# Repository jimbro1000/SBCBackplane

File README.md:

# HD6309 SBC Backplane

This projects defines a backplane expansion system
for the HD6309 Single Board Computer I designed 
(see https://github.com/jimbro1000/HD6309sbc)

Each backplane panel provides two slots for the 
100mm x 100mm expansion tiles plus a pair of 
"sideways" connector to add extra backplane panels 
to either side.

Hypothetically you could keep expanding but in 
real terms the drivers on each chip can only 
connect to a limit number of other chips, this
places real term limits of 4 - 6 tiles without
buffering, especially on the address and data
lines

## Tile layout

The positioning of connectors for the tiles is
defined by the layout of the main SBC tile, as
such it is essential that the relative position
of the two power and expansion connector of each
tile is maintained

### Alternative layouts

Provided the relative tile connector positions are 
maintained the layout of boards does not need to
be two dimensional.

## Power input

All of the tiles (so far) require +5V and ground.
It is expected that the primary tile provides the
power input from an external source, with good
regulation of power and current. Adding extra
tiles may place unexpected load and cause drop
outs or unpredictable behaviours

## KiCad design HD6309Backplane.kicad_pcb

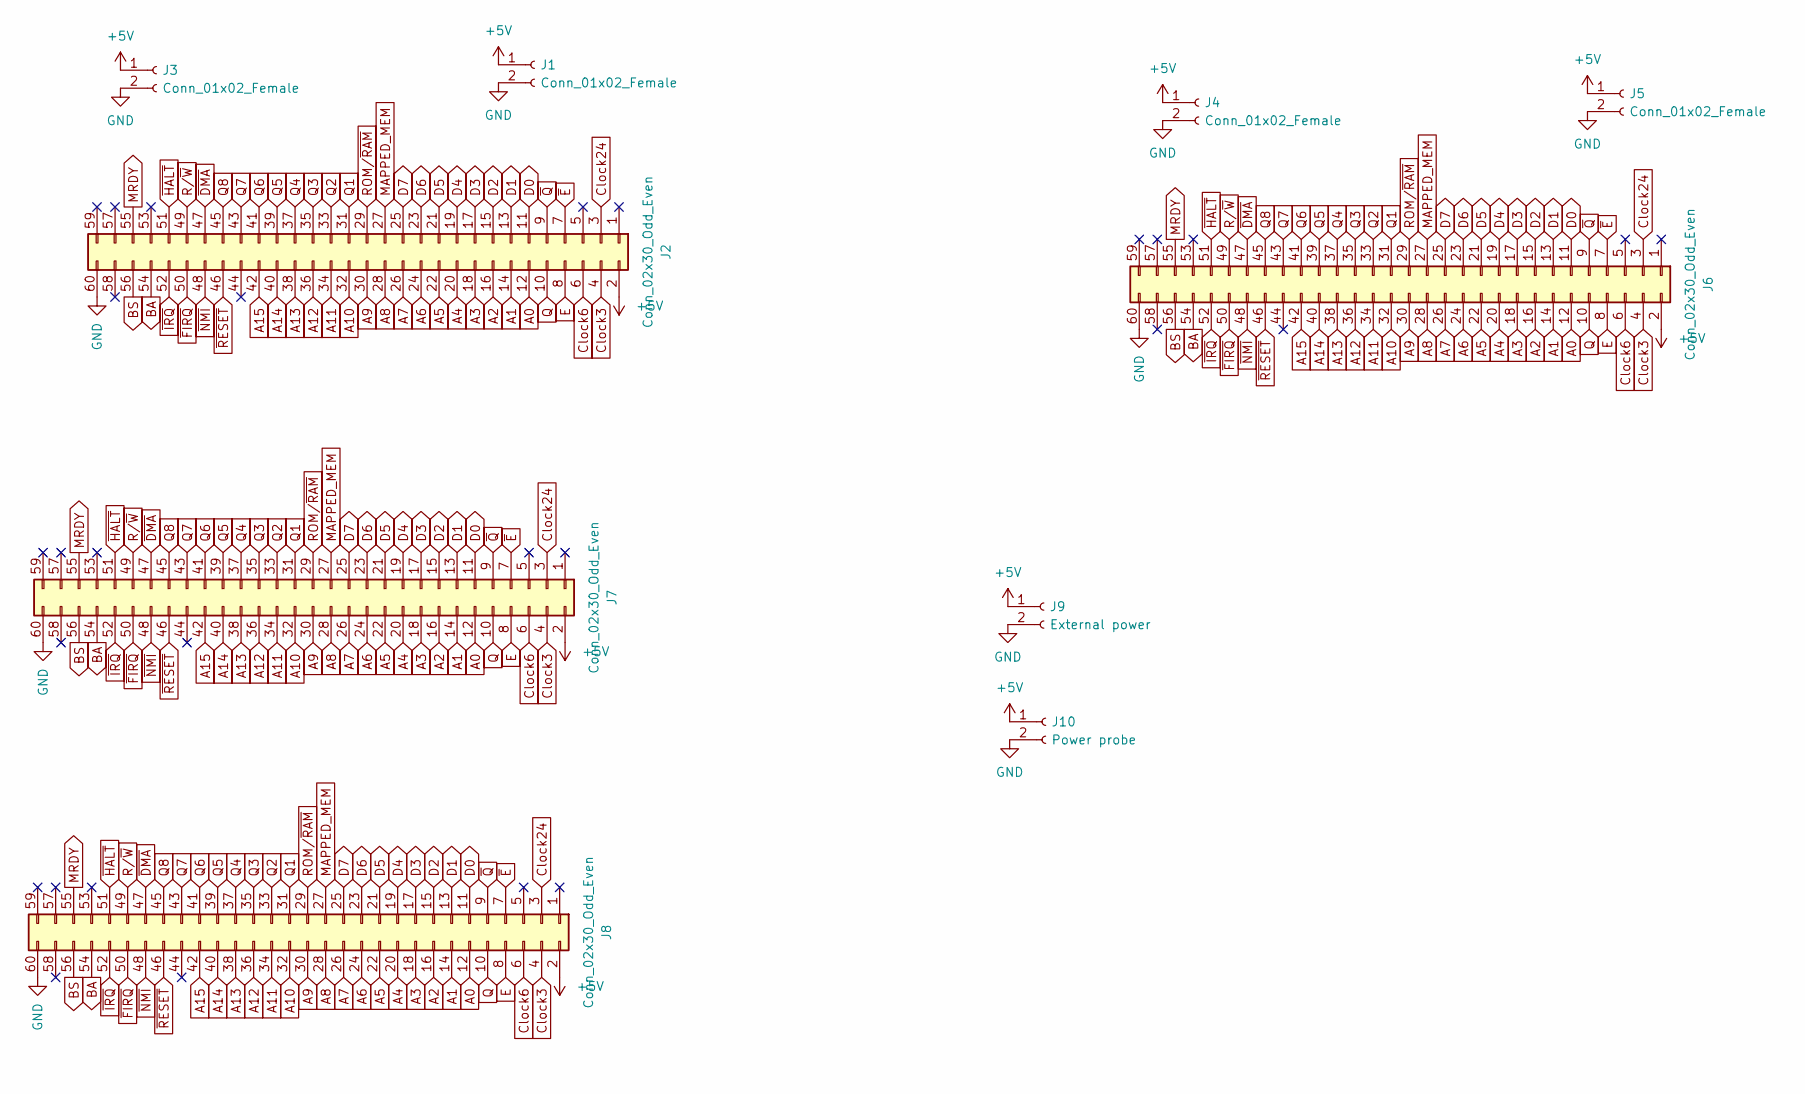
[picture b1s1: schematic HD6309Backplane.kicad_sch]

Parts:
J1, J3, J4, J5: Conn_01x02_Female; PinSocket_1x02_P2.54mm_Vertical
J2, J6, J7, J8: Conn_02x30_Odd_Even; PinSocket_2x30_P2.54mm_Vertical
J9: External power; PinSocket_1x02_P2.54mm_Vertical
J10: Power probe; PinSocket_1x02_P2.54mm_Vertical

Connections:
+5V: J1.1, J2.2, J3.1, J4.1, J5.1, J6.2, J7.2, J8.2, J9.1, J10.1
A0: J2.12, J6.12, J7.12, J8.12
A1: J2.14, J6.14, J7.14, J8.14
A2: J2.16, J6.16, J7.16, J8.16
A3: J2.18, J6.18, J7.18, J8.18
A4: J2.20, J6.20, J7.20, J8.20
A5: J2.22, J6.22, J7.22, J8.22
A6: J2.24, J6.24, J7.24, J8.24
A7: J2.26, J6.26, J7.26, J8.26
A8: J2.28, J6.28, J7.28, J8.28
A9: J2.30, J6.30, J7.30, J8.30
A10: J2.32, J6.32, J7.32, J8.32
A11: J2.34, J6.34, J7.34, J8.34
A12: J2.36, J6.36, J7.36, J8.36
A13: J2.38, J6.38, J7.38, J8.38
A14: J2.40, J6.40, J7.40, J8.40
A15: J2.42, J6.42, J7.42, J8.42
BA: J2.54, J6.54, J7.54, J8.54
BS: J2.56, J6.56, J7.56, J8.56
Clock3: J2.4, J6.4, J7.4, J8.4
Clock6: J2.6, J6.6, J7.6, J8.6
Clock24: J2.3, J6.3, J7.3, J8.3
D0: J2.11, J6.11, J7.11, J8.11
D1: J2.13, J6.13, J7.13, J8.13
D2: J2.15, J6.15, J7.15, J8.15
D3: J2.17, J6.17, J7.17, J8.17
D4: J2.19, J6.19, J7.19, J8.19
D5: J2.21, J6.21, J7.21, J8.21
D6: J2.23, J6.23, J7.23, J8.23
D7: J2.25, J6.25, J7.25, J8.25
E: J2.8, J6.8, J7.8, J8.8
GND: J1.2, J2.60, J3.2, J4.2, J5.2, J6.60, J7.60, J8.60, J9.2, J10.2
MAPPED_MEM: J2.27, J6.27, J7.27, J8.27
MRDY: J2.55, J6.55, J7.55, J8.55
Q: J2.10, J6.10, J7.10, J8.10
Q1: J2.31, J6.31, J7.31, J8.31
Q2: J2.33, J6.33, J7.33, J8.33
Q3: J2.35, J6.35, J7.35, J8.35
Q4: J2.37, J6.37, J7.37, J8.37
Q5: J2.39, J6.39, J7.39, J8.39
Q6: J2.41, J6.41, J7.41, J8.41
Q7: J2.43, J6.43, J7.43, J8.43
Q8: J2.45, J6.45, J7.45, J8.45
ROM/~RAM: J2.29, J6.29, J7.29, J8.29
R/~W: J2.49, J6.49, J7.49, J8.49
~DMA: J2.47, J6.47, J7.47, J8.47
~E: J2.7, J6.7, J7.7, J8.7
~FIRQ: J2.50, J6.50, J7.50, J8.50
~HALT: J2.51, J6.51, J7.51, J8.51
~IRQ: J2.52, J6.52, J7.52, J8.52
~NMI: J2.48, J6.48, J7.48, J8.48
~Q: J2.9, J6.9, J7.9, J8.9
~RESET: J2.46, J6.46, J7.46, J8.46

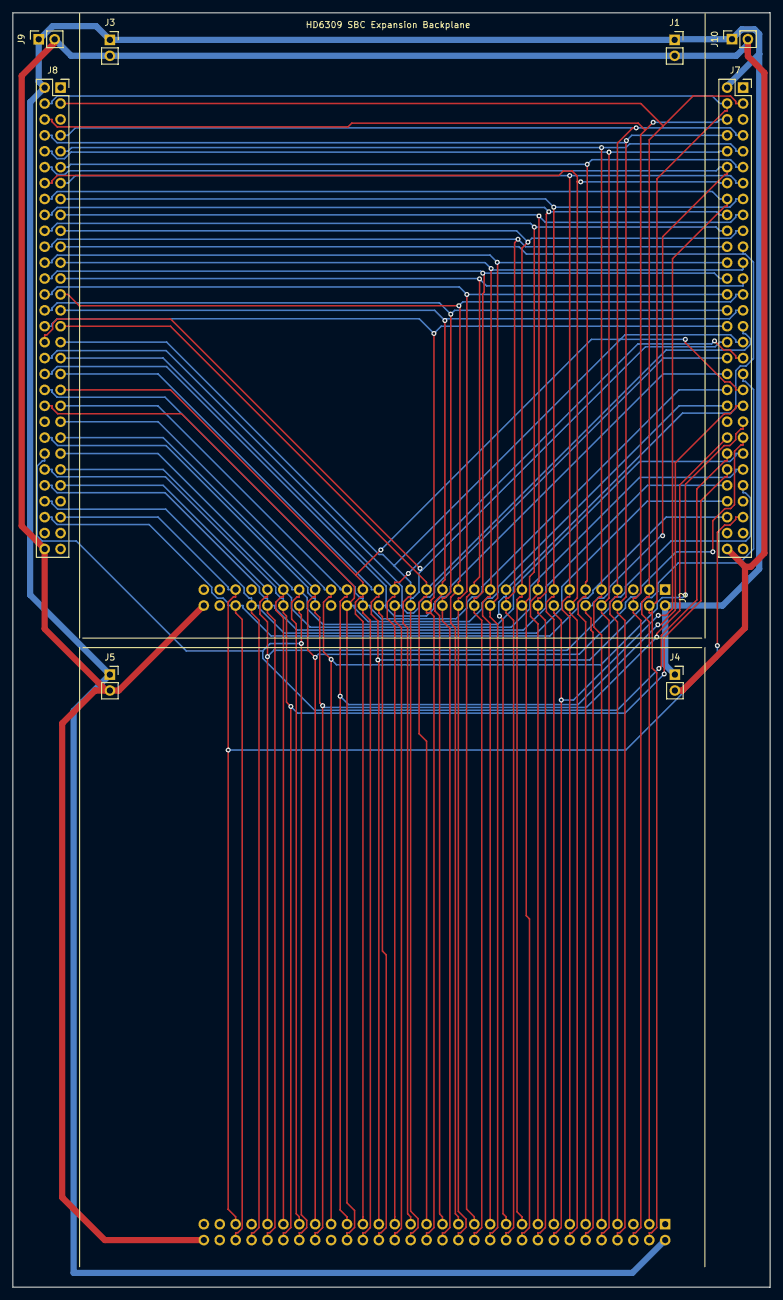
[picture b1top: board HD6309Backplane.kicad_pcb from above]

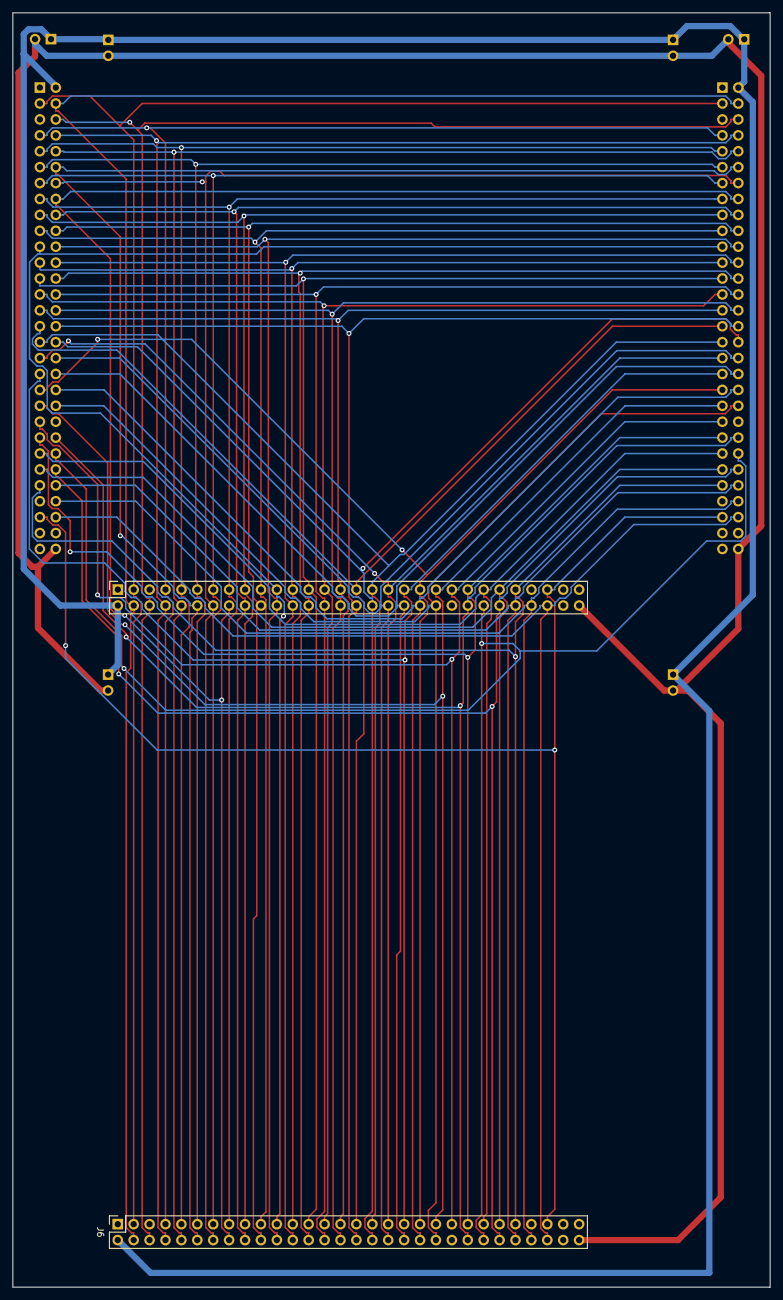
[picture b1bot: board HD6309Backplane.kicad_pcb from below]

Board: 2 copper layers, 120.9 x 203.5 mm, 10 parts (2 on the bottom side), 53 nets.

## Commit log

2022-10-06 align to new expansion position
2022-10-08 add mapped memory lane
2023-01-15 refresh
